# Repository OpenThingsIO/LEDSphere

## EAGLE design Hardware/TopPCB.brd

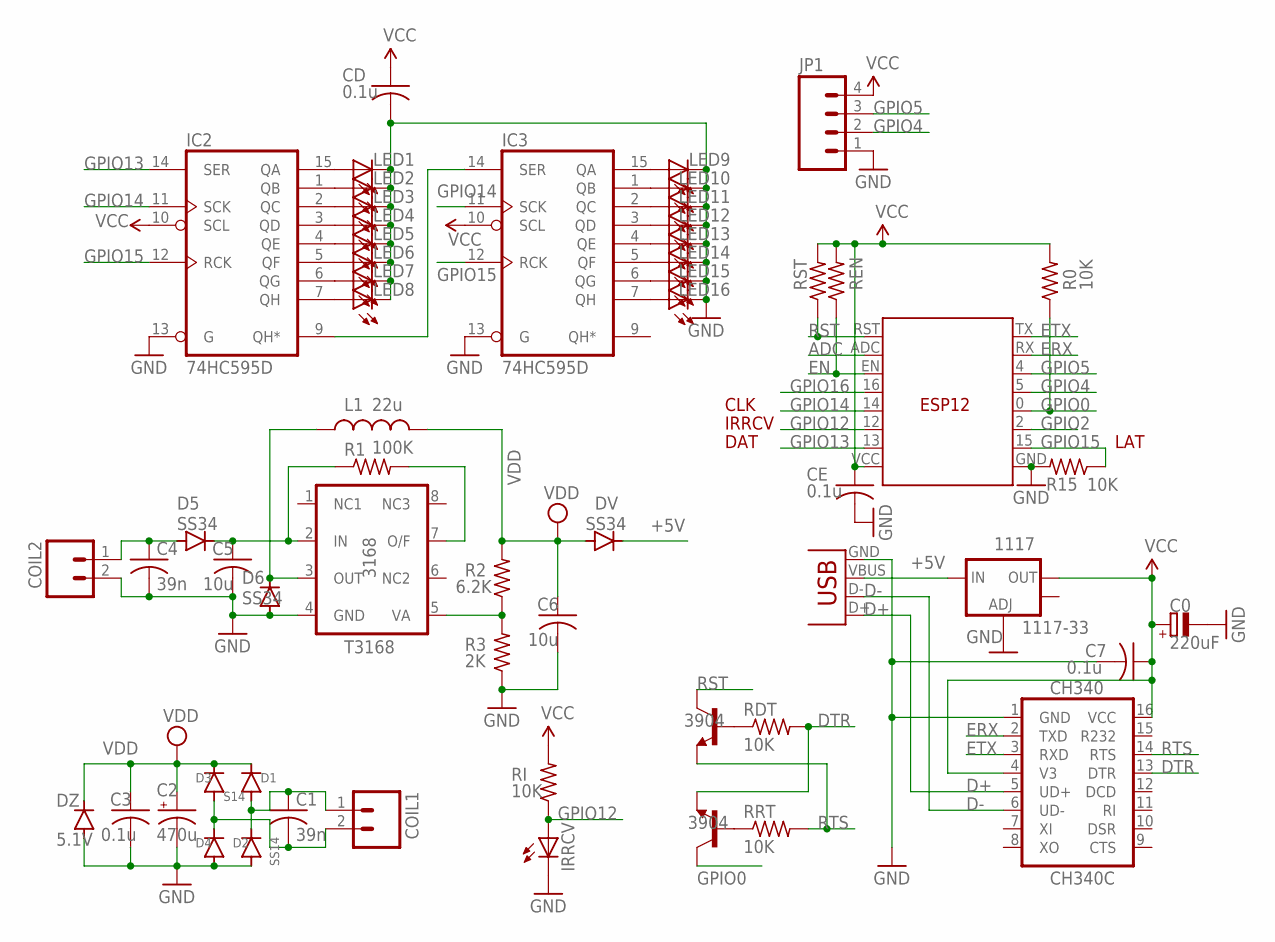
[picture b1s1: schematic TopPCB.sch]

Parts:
1117: 1117-33; SOT223
3168: T3168; SO08
C0: 220uF; CT3528
C1, C4: 39n; C0805K
C2: 470u; E2,5-6
C3: 0.1u; C0805K
C5, C6: 10u; C0805K
C7: 0.1u; C0603K
CD: 0.1u; C0603K
CE: 0.1u; C0603K
CH340: CH340C; SO16
COIL1, COIL2: M021X02_NO_SILK; 1X02_NO_SILK
D1: S14; DO-214AC
D2, D3, D4: SS14; DO-214AC
D5, D6: SS34; DO-214AC
DV: SS34; DO-214AC
DZ: 5.1V; MINIMELF
ESP: ESP; ESP12
IC2, IC3: 74HC595D; SO16
IRRCV: LED3MM
JP1: M041X04_NO_SILK; 1X04_NO_SILK
L1: 22u; CR54
LED1, LED2, LED3, LED4, LED5, LED6, LED7, LED8, LED9, LED10, LED11, LED12, LED13, LED14, LED15, LED16: LEDCHIPLED_0805; CHIPLED_0805
R0, R15: 10K; R0603
R1: 100K; R0603
R2: 6.2K; R0603
R3: 2K; R0603
RDT: 10K; R0603
REN: 10K; R0603
RI: 10K; R0603
RRT: 10K; R0603
RST: 10K; R0603
T1, T2: 3904; SOT23-BEC
X3: USBMICROB2; USB-MICROB2

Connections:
+5V: 1117.3 (IN), DV.C, X3.VBUS
ADC: ESP.ADC
D+: CH340.5 (UD+), X3.D+
D-: CH340.6 (UD-), X3.D-
DTR: CH340.13 (DTR), RDT.2, T2.E
EN: ESP.EN, REN.1
ERX: CH340.2 (TXD), ESP.RX
ETX: CH340.3 (RXD), ESP.TX
GND: 1117.1 (ADJ), 3168.4 (GND), C0.-, C2.-, C3.2, C4.2, C5.2, C6.2, C7.2, CD.2, CE.2, CH340.1 (GND), COIL2.2, D2.A, D4.A, D6.A, DZ.A, ESP.GND, IC2.8 (GND), IC2.13 (G), IC3.8 (GND), IC3.13 (G), IRRCV.K (C), JP1.1, LED1.C, LED2.C, LED3.C, LED4.C, LED5.C, LED6.C, LED7.C, LED8.C, LED9.C, LED10.C, LED11.C, LED12.C, LED13.C, LED14.C, LED15.C, LED16.C, R3.1, R15.2, X3.GND
GPIO0: ESP.0 (G0), R0.1, T2.C
GPIO2: ESP.2 (G2)
GPIO4: ESP.5 (G5), JP1.2
GPIO5: ESP.4 (G4), JP1.3
GPIO12: ESP.12 (G12), IRRCV.A, RI.1
GPIO13: ESP.13 (G13), IC2.14 (SER)
GPIO14: ESP.14 (G14), IC2.11 (SCK), IC3.11 (SCK)
GPIO15: ESP.15 (G15), IC2.12 (RCK), IC3.12 (RCK), R15.1
GPIO16: ESP.16 (G16)
unnamed: 3168.7 (O/F), R1.2
unnamed: C1.2, COIL1.2, D3.A, D4.C
unnamed: C4.1, COIL2.1, D5.A
unnamed: 3168.2 (IN), C5.1, D5.C, R1.1
unnamed: IC2.1 (QB), LED2.A
unnamed: C1.1, COIL1.1, D1.A, D2.C
unnamed: 3168.5 (VA), R2.1, R3.2
unnamed: 3168.3 (OUT), D6.C, L1.P$1 (1)
unnamed: IC2.15 (QA), LED1.A
unnamed: IC2.2 (QC), LED3.A
unnamed: IC2.3 (QD), LED4.A
unnamed: RDT.1, T1.B
unnamed: RRT.1, T2.B
unnamed: IC2.4 (QE), LED5.A
unnamed: IC2.5 (QF), LED6.A
unnamed: IC2.6 (QG), LED7.A
unnamed: IC2.7 (QH), LED8.A
unnamed: IC3.15 (QA), LED9.A
unnamed: IC3.1 (QB), LED10.A
unnamed: IC3.2 (QC), LED11.A
unnamed: IC3.3 (QD), LED12.A
unnamed: IC3.4 (QE), LED13.A
unnamed: IC3.5 (QF), LED14.A
unnamed: IC3.6 (QG), LED15.A
unnamed: IC3.7 (QH), LED16.A
unnamed: IC2.9 (QH*), IC3.14 (SER)
RST: ESP.RST, RST.1, T1.C
RTS: CH340.14 (RTS), RRT.2, T1.E
VCC: 1117.2 (OUT), C0.+, C7.1, CD.1, CE.1, CH340.4 (V3), CH340.16 (VCC), ESP.VCC, IC2.10 (SCL), IC2.16 (VCC), IC3.10 (SCL), IC3.16 (VCC), JP1.4, R0.2, REN.2, RI.2, RST.2
VDD: C2.+, C3.1, C6.1, D1.C, D3.C, DV.A, DZ.C, L1.P$2 (2), R2.2

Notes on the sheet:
IRRCV
DAT
CLK
LAT

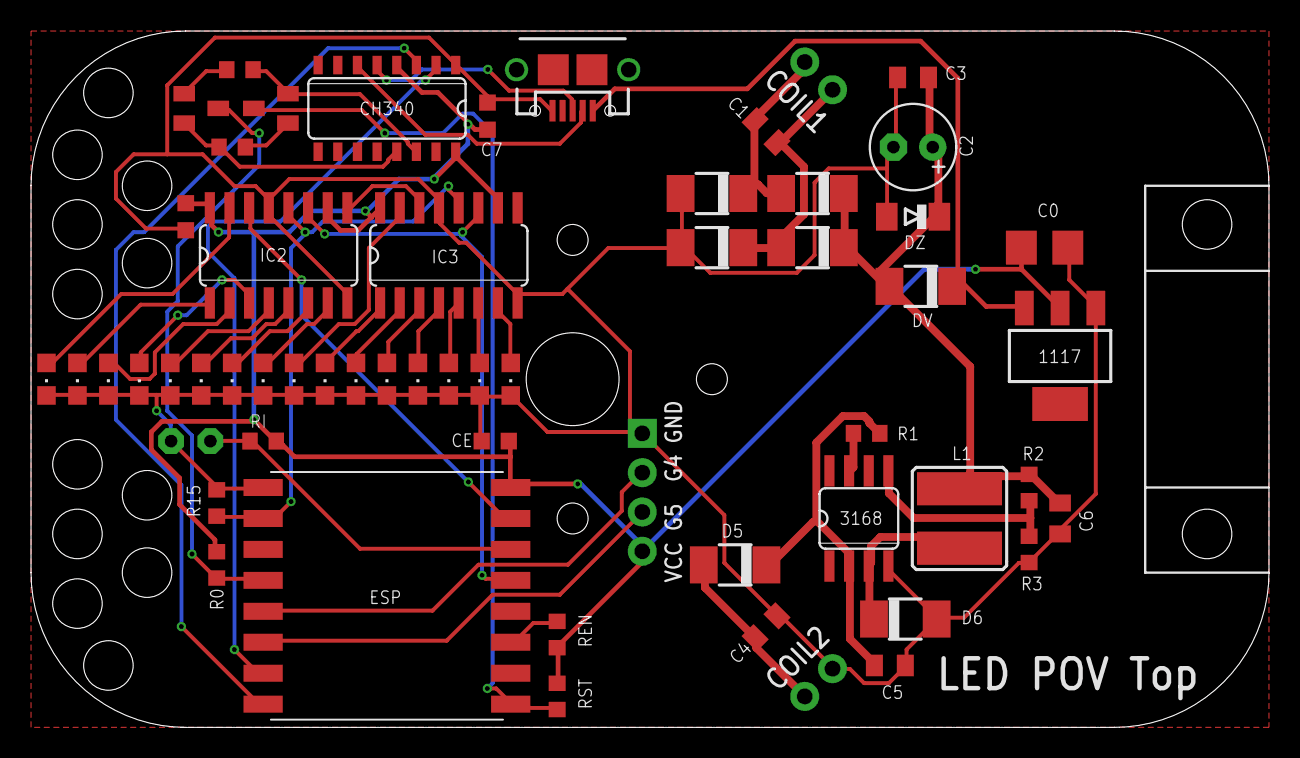
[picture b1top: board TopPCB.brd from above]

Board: 2 copper layers, 80.0 x 45.0 mm, 58 parts (1 on the bottom side), 45 nets.

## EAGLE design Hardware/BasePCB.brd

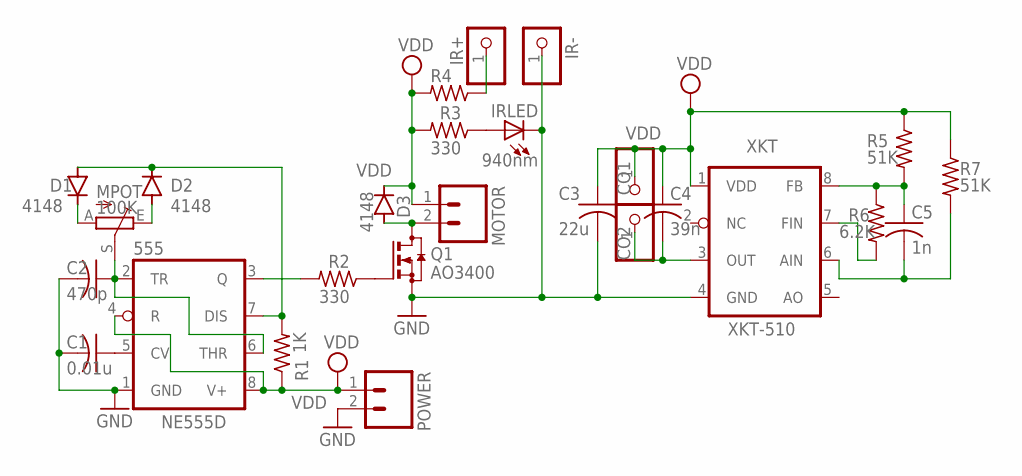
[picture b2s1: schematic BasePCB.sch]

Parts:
555: NE555D; SO08
C1: 0.01u; C0603K
C2: 470p; C0603K
C3: 22u; C0805K
C4: 39n; C0805K
C5: 1n; C0805K
CO1, CO2: PINHD-1X1CB; 1X01-CLEANBIG
D1, D2, D3: 4148; MINIMELF
IR+: PINHD-1X1CB; 1X01-CLEANBIG
IR-: PINHD-1X1CB; 1X01-CLEANBIG
IRLED: 940nm; CHIPLED_0603
MOTOR: M021X02_NO_SILK; 1X02_NO_SILK
MPOT: 100K; CA6V
POWER: M021X02_NO_SILK; 1X02_NO_SILK
Q1: AO3400; SOT23
R1: 1K; R0603
R2, R3, R4: 330; R0603
R5, R7: 51K; R0603
R6: 6.2K; R0603
XKT: XKT-510; SO08

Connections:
GND: 555.1 (GND), C1.2, C2.2, C3.2, IR-.1, IRLED.C, POWER.2, Q1.2 (S), XKT.4 (GND)
unnamed: 555.5 (CV), C1.1
unnamed: D1.C, MPOT.A
unnamed: 555.3 (Q), R2.2
unnamed: 555.2 (TR), 555.6 (THR), C2.1, MPOT.S
unnamed: D2.A, MPOT.E
unnamed: 555.7 (DIS), D1.A, D2.C, R1.2
unnamed: Q1.1 (G), R2.1
unnamed: D3.A, MOTOR.2, Q1.3 (D)
unnamed: IRLED.A, R3.1
unnamed: IR+.1, R4.1
unnamed: C5.1, R5.2, R6.1, XKT.8 (FB)
unnamed: C4.2, CO2.1, XKT.3 (OUT)
unnamed: C5.2, R7.2, XKT.6 (AIN)
unnamed: R6.2, XKT.7 (FIN)
VDD: 555.4 (R), 555.8 (V+), C3.1, C4.1, CO1.1, D3.C, MOTOR.1, POWER.1, R1.1, R3.2, R4.2, R5.1, R7.1, XKT.1 (VDD)

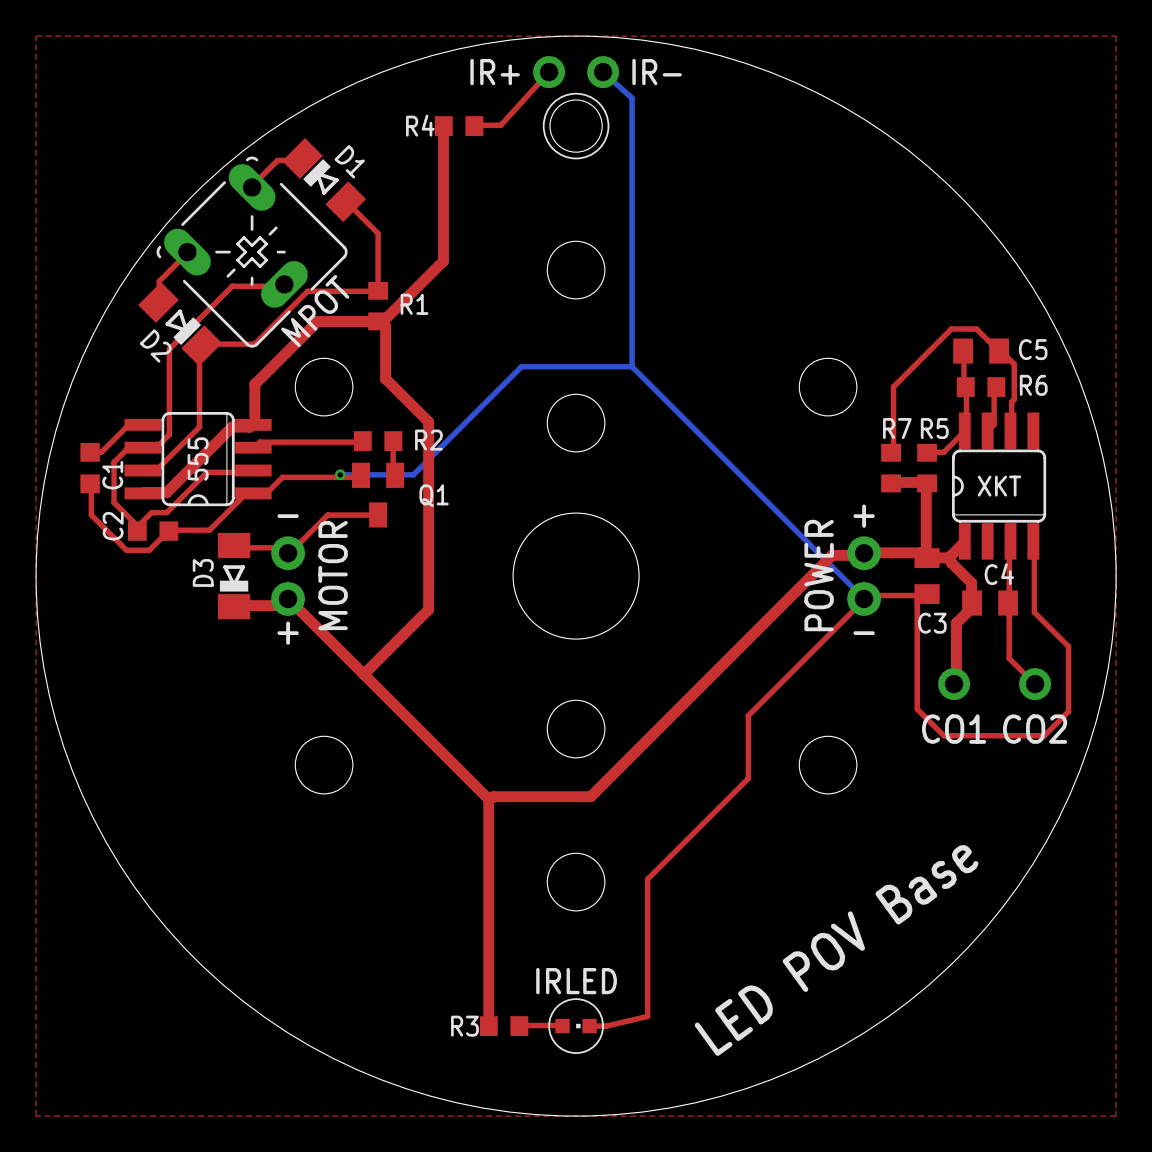
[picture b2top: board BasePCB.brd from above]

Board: 2 copper layers, 60.0 x 60.0 mm, 26 parts (0 on the bottom side), 16 nets.

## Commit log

2019-12-24 initial checkin
2019-12-28 add text scrolling demo
2020-01-07 add first version of PCB design
2020-01-07 remove lock files
2020-01-08 stl file: prototype for the arc
    prototype with a slit to slide the LED strip into. This also has a tiny piece so that it can be screwed onto the top PCB. It can be made thinner (to use less plastic per print) but this is just to se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

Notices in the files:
parts and their libraries:
SparkFunNew: Licensing: CC v3.0 Share-Alike You are welcome to use this library for commercial purposes.
